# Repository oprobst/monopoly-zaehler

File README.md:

# monopoly-zaehler

Ein elektronischer Zähler für Monopoly auf einem Microcontroller.

Wird in ein UW-Gehäuse gepackt und mittels Reedschaltern bedient.

Details siehe
http://www.tief-dunkel-kalt.org/index.php/blog/45-unterwasser-monopoly

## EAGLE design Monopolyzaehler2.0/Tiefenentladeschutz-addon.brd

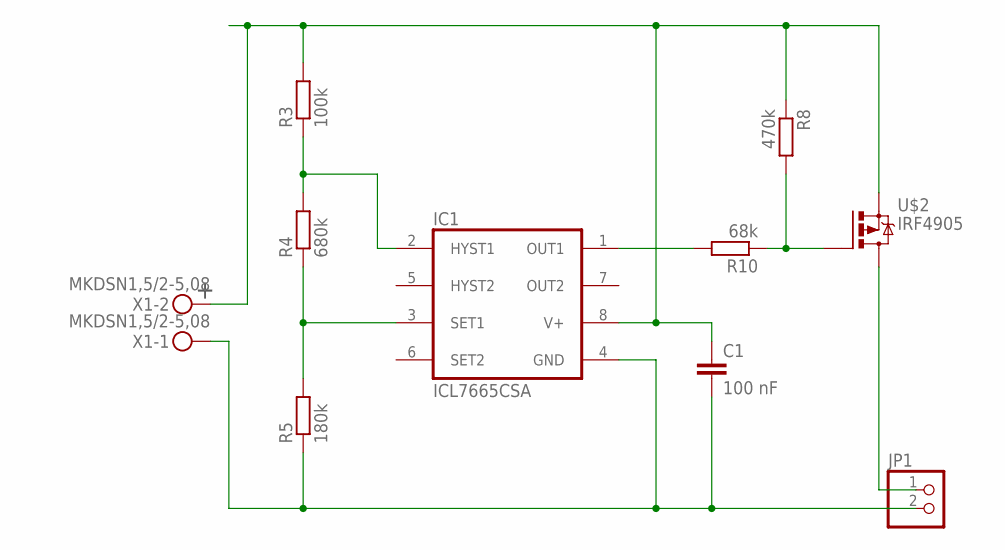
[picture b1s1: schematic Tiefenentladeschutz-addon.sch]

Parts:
C1: 100 nF; C0603
IC1: ICL7665CSA; SO08
JP1: PINHD-1X2; 1X02
R3: 100k; R1206
R4: 680k; R1206
R5: 180k; R1206
R8: 470k; R1206
R10: 68k; R1206
U$2: IRF4905; TO220BH
X1: MKDSN1,5/2-5,08

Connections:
GND: C1.2, IC1.4 (GND), JP1.2, R5.1, X1.1
unnamed: IC1.3 (SET1), R4.1, R5.2
unnamed: R8.2, R10.1, U$2.G
unnamed: IC1.2 (HYST1), R3.1, R4.2
unnamed: IC1.1 (OUT1), R10.2
unnamed: JP1.1, U$2.D
V+: C1.1, IC1.8 (V+), R3.2, R8.1, U$2.S, X1.2

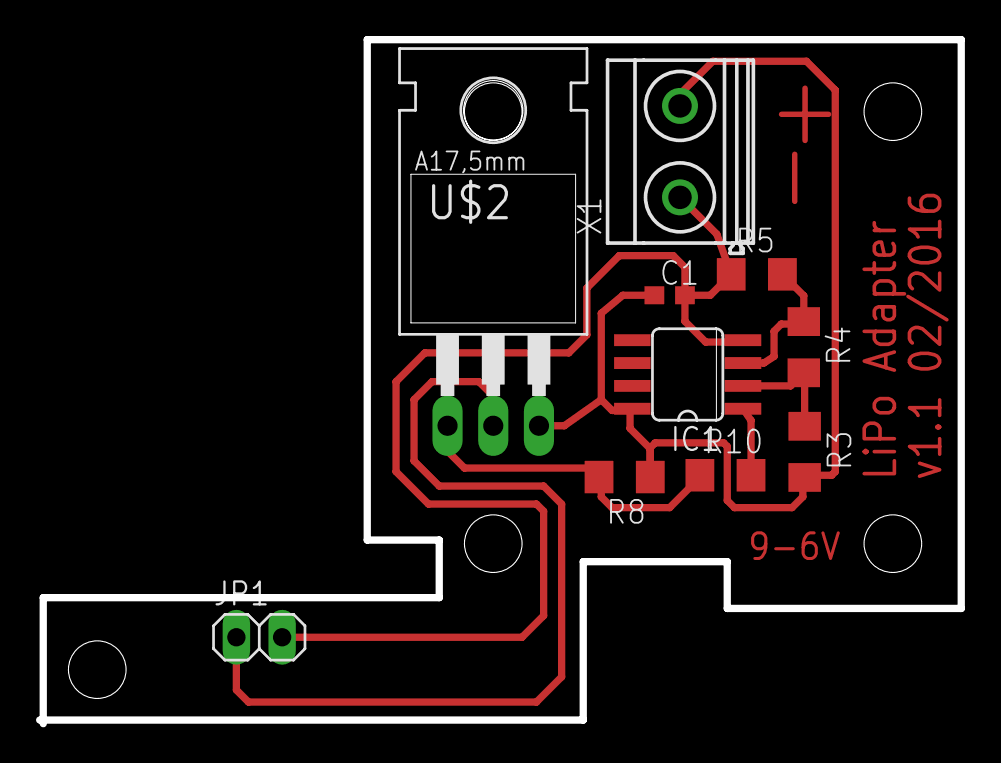
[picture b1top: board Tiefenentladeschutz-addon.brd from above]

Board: 2 copper layers, 51.2 x 38.0 mm, 10 parts (0 on the bottom side), 7 nets.

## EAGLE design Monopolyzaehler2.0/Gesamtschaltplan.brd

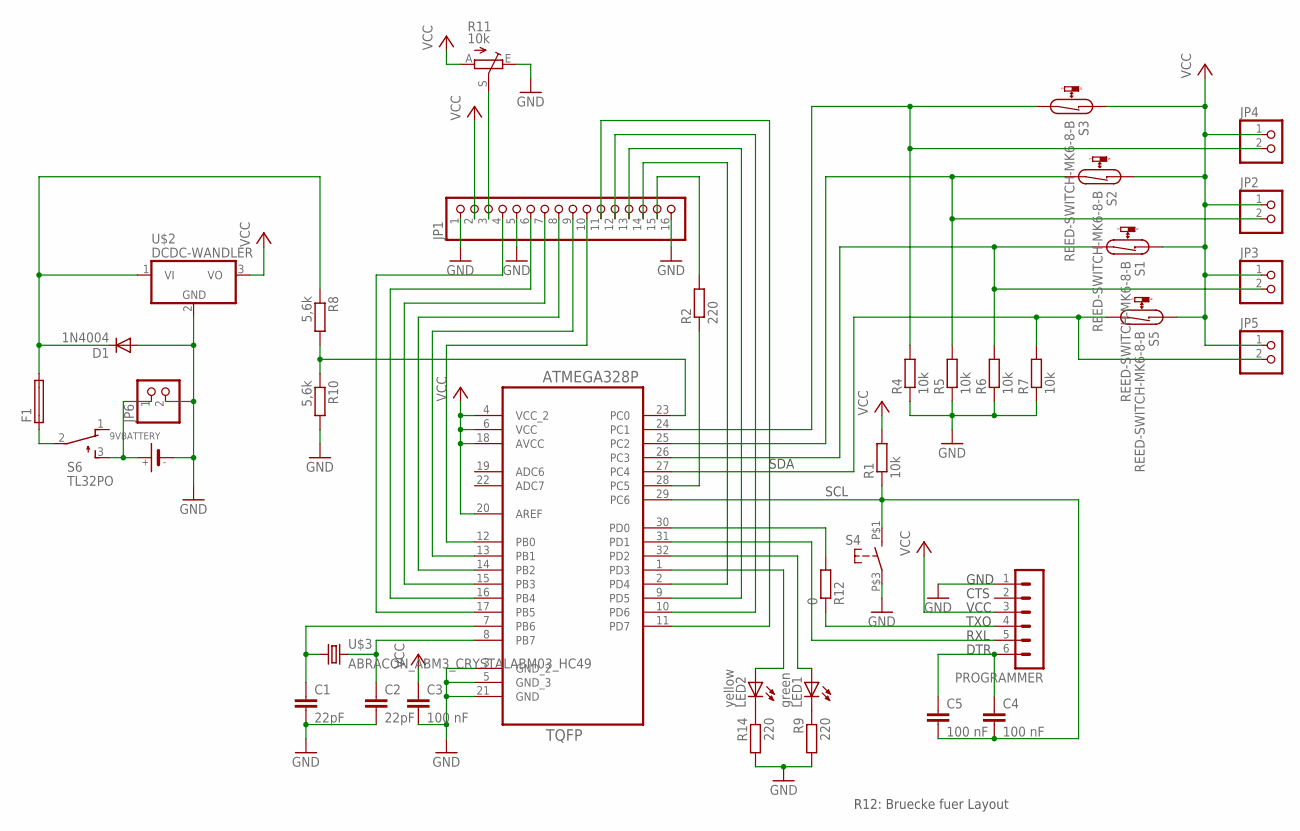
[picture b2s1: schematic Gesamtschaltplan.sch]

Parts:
C1, C2: 22pF; C0603K
C3, C4, C5: 100 nF; C0603
D1: 1N4004; DO41-10
F1: SH22,5A
IC1: ATMEGA328P-AU; QFP80P900X900X120-32N
JP1: PINHD-1X16; 1X16
JP2, JP3, JP4, JP5, JP6: PINHD-1X2; 1X02
LED1: green; LED3MM
LED2: yellow; LED3MM
PROGRAMMER: MA06-1
R1, R4, R5, R6, R7: 10k; R1206
R2, R9, R14: 220; R1206
R8, R10: 5,6k; R1206
R11: 10k; PT-10
R12: 0; R1206
S1, S2, S3, S5: REED-SWITCH-MK6-8-B; MK6-8-A
S4: SCHLIESSER_TASTSCHALTER; NAMAE-JTP-1130
S6: TL32PO; TL3XPO
U$1: 9VBATTERY; BATTERIEHALTER-54X30
U$2: DCDC-WANDLER; TRACOPOWER-DCDCWANDER-TSR1
U$3: ABRACON_ABM3_CRYSTALABM03_HC49; ABM03_HC49

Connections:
GND: C1.2, C2.2, C3.2, D1.A, IC1.3 (GND_2), IC1.5 (GND_3), IC1.21 (GND), JP1.1, JP1.5, JP1.16, JP6.2, PROGRAMMER.1, R4.1, R5.1, R6.1, R7.1, R9.2, R10.2, R11.E, R14.2, S4.P$3 (4), U$1.P$2, U$2.2 (GND)
unnamed: C4.2, C5.2, IC1.29 (PC6), R1.1, S4.P$1 (3)
unnamed: LED2.K (C), R14.1
unnamed: C2.1, IC1.8 (PB7), U$3.2
unnamed: C1.1, IC1.7 (PB6), U$3.1
unnamed: IC1.2 (PD4), JP1.14
unnamed: F1.1, S6.2
unnamed: IC1.1 (PD3), LED2.A
unnamed: IC1.9 (PD5), JP1.13
unnamed: IC1.32 (PD2), LED1.A
unnamed: IC1.12 (PB0), JP1.10
unnamed: D1.C, F1.2, R8.1, U$2.1 (VI)
unnamed: IC1.13 (PB1), JP1.9
unnamed: IC1.27 (PC4), JP5.2, R7.2, S5.2
unnamed: IC1.26 (PC3), JP3.2, R6.2, S1.2
unnamed: IC1.25 (PC2), JP2.2, R5.2, S2.2
unnamed: IC1.24 (PC1), JP4.2, R4.2, S3.2
unnamed: IC1.10 (PD6), JP1.12
unnamed: JP1.3, R11.S
unnamed: JP6.1, S6.3 (S), U$1.P$1
unnamed: LED1.K (C), R9.1
unnamed: IC1.11 (PD7), JP1.11
unnamed: PROGRAMMER.4, R12.1
unnamed: IC1.14 (PB2), JP1.8
unnamed: IC1.15 (PB3), JP1.7
unnamed: IC1.16 (PB4), JP1.6
unnamed: IC1.17 (PB5), JP1.4
unnamed: IC1.23 (PC0), R8.2, R10.1
unnamed: C4.1, C5.1, PROGRAMMER.6
unnamed: IC1.31 (PD1), PROGRAMMER.5
unnamed: IC1.28 (PC5), R2.1
unnamed: IC1.30 (PD0), R12.2
unnamed: JP1.15, R2.2
VCC: C3.1, IC1.4 (VCC_2), IC1.6 (VCC), IC1.18 (AVCC), IC1.20 (AREF), JP1.2, JP2.1, JP3.1, JP4.1, JP5.1, PROGRAMMER.3, R1.2, R11.A, S1.1, S2.1, S3.1, S5.1, U$2.3 (VO)

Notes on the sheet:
SDA
SCL
DTR
RXL
TXO
VCC
CTS
GND
R12: Bruecke fuer Layout

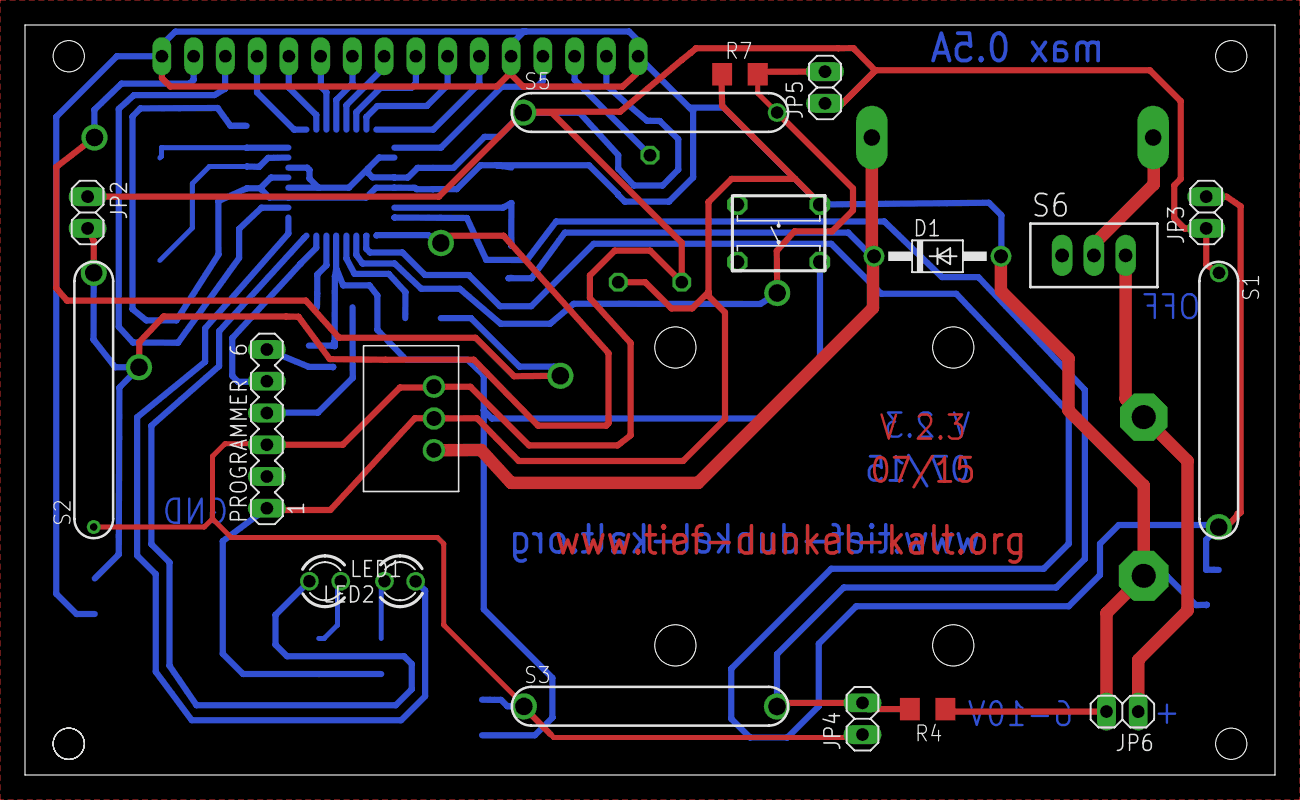
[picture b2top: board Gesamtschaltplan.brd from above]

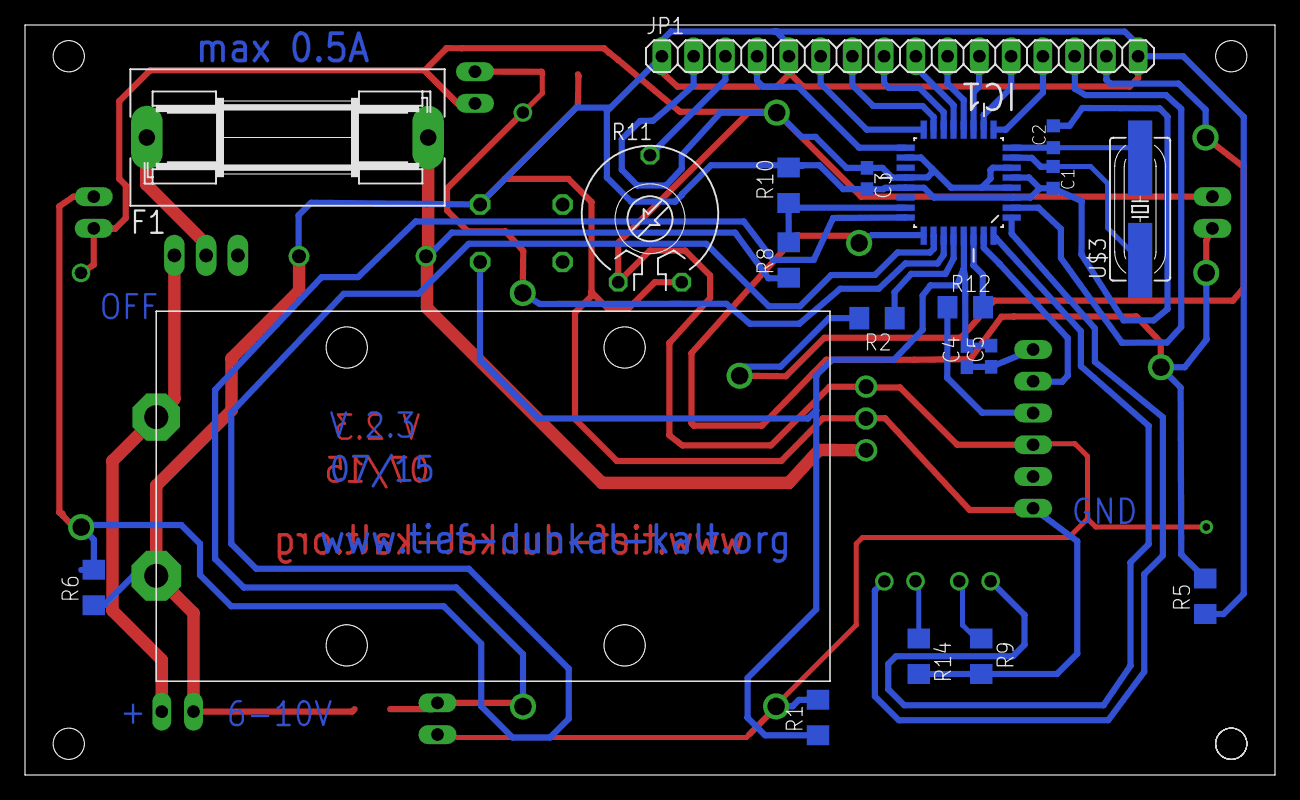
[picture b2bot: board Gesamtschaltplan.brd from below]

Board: 2 copper layers, 100.0 x 60.0 mm, 38 parts (20 on the bottom side), 34 nets.

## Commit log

2015-06-28 initial check in
2015-06-28 initial checkin
2015-06-29 Bildschirmschoner
2015-07-01 zaehler fuer laufzeit zugefuegt waeehrung auf dollar umgestellt
2016-02-15 Added low voltage detection module for lipo
2016-09-18 Laufzeit counter added
2016-09-18 Addon für Tiefenentladeschutz LiPo
2016-09-18 Added link to website
2017-06-06 Commit of CAD Model for dive base
    Deleted gcode
